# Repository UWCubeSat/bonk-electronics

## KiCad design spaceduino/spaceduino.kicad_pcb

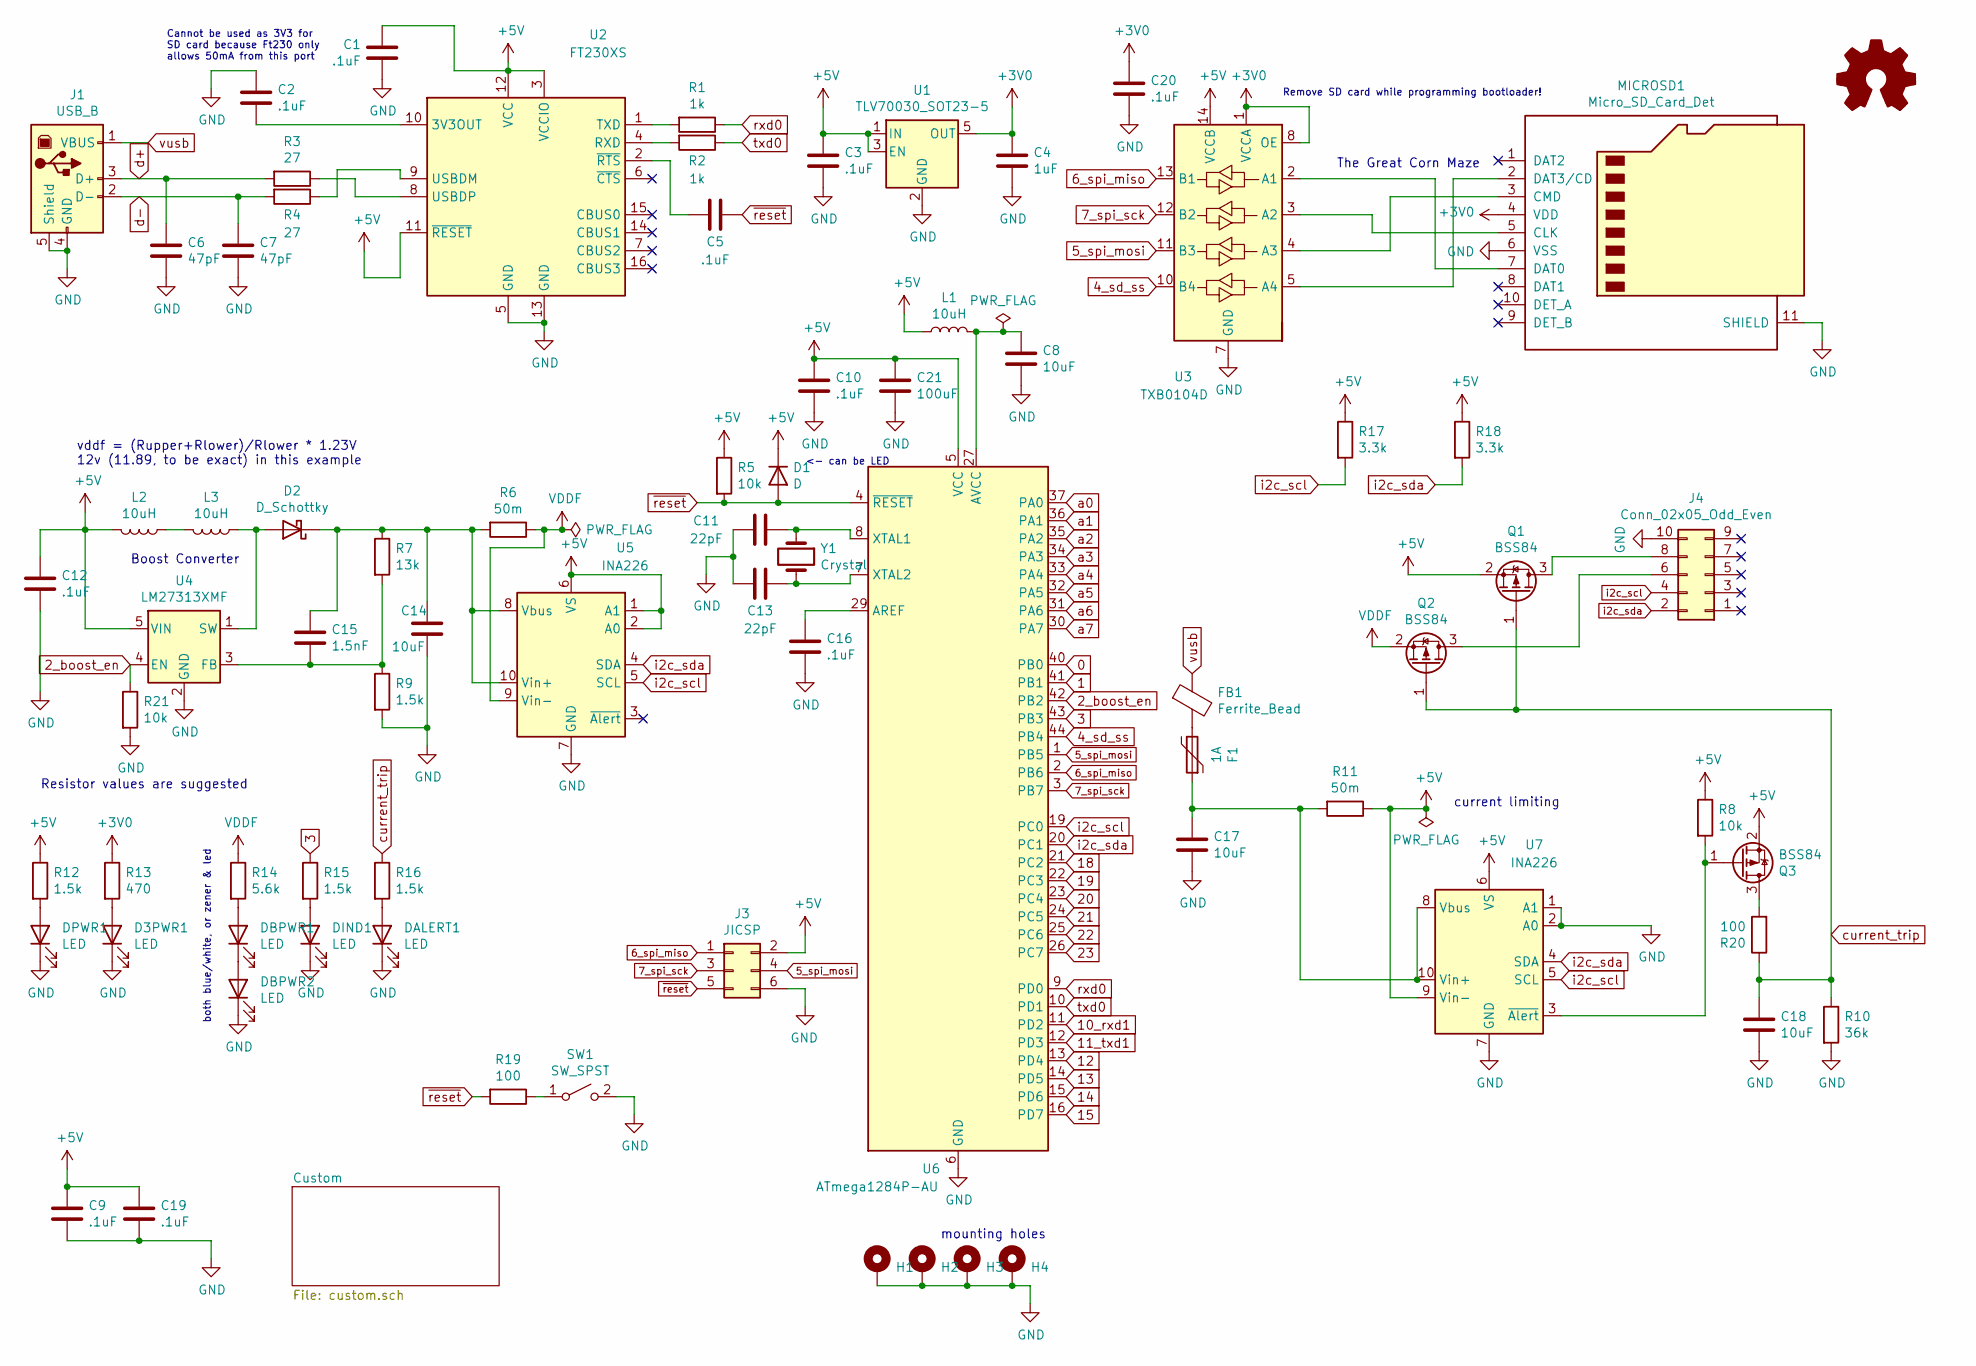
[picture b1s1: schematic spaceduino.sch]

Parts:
C1, C2, C3, C5, C9, C10, C12, C16, C19, C20: .1uF; C_0603_1608Metric; LCSC C77055
C4: 1uF; C_1206_3216Metric; LCSC C141215
C6, C7: 47pF; C_0603_1608Metric; LCSC C1671
C8, C14, C17, C18: 10uF; C_1206_3216Metric; LCSC C14860
C11, C13: 22pF; C_0603_1608Metric; LCSC C599690
C15: 1.5nF; C_0603_1608Metric; LCSC C519421
C21: 100uF; C_Radial_D5.0mm_H11.0mm_P2.00mm
D1: D; D_SOD-123
D2: D_Schottky; D_SOD-123; LCSC C222352
D3PWR1: LED; LED_1206_3216Metric; LCSC C192676
DALERT1: LED; LED_1206_3216Metric; LCSC C192676
DBPWR1, DBPWR2: LED; LED_1206_3216Metric; LCSC C192676
DIND1: LED; LED_1206_3216Metric; LCSC C192676
DPWR1: LED; LED_1206_3216Metric; LCSC C192676
F1: 1A; Fuse_1206_3216Metric; LCSC C315895
FB1: Ferrite_Bead; L_1206_3216Metric; LCSC C88995
H1, H2, H3, H4: MountingHole_Pad; MountingHole_2.2mm_M2_Pad
J1: USB_B; usb-type-b; Digikey 732-2734-ND
J3: JICSP; PinHeader_2x03_P2.54mm_Vertical
J4: Conn_02x05_Odd_Even; PinHeader_2x05_P2.54mm_Vertical
L1, L2, L3: 10uH; L_1210_3225Metric; LCSC C86073
LOGO1: Logo_Open_Hardware_Small; spaceduino-logo
MICROSD1: Micro_SD_Card_Det; HRS_DM3CS-SF; LCSC C202111
Q1, Q2, Q3: BSS84; SOT-23; LCSC C508197
R1, R2: 1k; R_1206_3216Metric; LCSC C52199
R3, R4: 27; R_1206_3216Metric; LCSC C17946
R5, R8, R21: 10k; R_1206_3216Metric; LCSC C17902
R6, R11: 50m; R_1206_3216Metric
R7: 13k; R_1206_3216Metric; LCSC C34847
R9, R12, R15, R16: 1.5k; R_1206_3216Metric; LCSC C26030
R10: 36k; R_1206_3216Metric; LCSC C18007
R13: 470; R_1206_3216Metric; LCSC C4502
R14: 5.6k; R_1206_3216Metric; LCSC C18028
R17, R18: 3.3k; R_1206_3216Metric; LCSC C26032
R19, R20: 100; R_1206_3216Metric; LCSC C17901
SW1: SW_SPST; SolderJumper-2_P1.3mm_Open_TrianglePad1.0x1.5mm
U1: TLV70030_SOT23-5; SOT-23-5; Digikey 296-32412-1-ND
U2: FT230XS; SSOP-16_3.9x4.9mm_P0.635mm; Digikey 768-1135-1-ND
U3: TXB0104D; TSSOP-14_4.4x5mm_P0.65mm; Digikey 296-21928-1-ND
U4: LM27313XMF; SOT-23-5
U5, U7: INA226; VSSOP-10_3x3mm_P0.5mm
U6: ATmega1284P-AU; TQFP-44_10x10mm_P0.8mm; Digikey ATMEGA1284P-AURCT-ND
Y1: Crystal; Crystal_HC49-U_Vertical

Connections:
0: U6.40 (PB0)
1: U6.41 (PB1)
2_boost_en: R21.1, U4.4 (EN), U6.42 (PB2)
3: R15.1, U6.43 (PB3)
4_sd_ss: U3.10 (B4), U6.44 (PB4)
5_spi_mosi: J3.4, U3.11 (B3), U6.1 (PB5)
6_spi_miso: J3.1, U3.13 (B1), U6.2 (PB6)
7_spi_sck: J3.3, U3.12 (B2), U6.3 (PB7)
10_rxd1: U6.11 (PD2)
11_txd1: U6.12 (PD3)
12: U6.13 (PD4)
13: U6.14 (PD5)
14: U6.15 (PD6)
15: U6.16 (PD7)
18: U6.21 (PC2)
19: U6.22 (PC3)
20: U6.23 (PC4)
21: U6.24 (PC5)
22: U6.25 (PC6)
23: U6.26 (PC7)
+3V0: C4.1, C20.1, MICROSD1.4 (VDD), R13.1, U1.5 (OUT), U3.1 (VCCA), U3.8 (OE)
+5V: C1.1, C3.1, C9.1, C10.1, C12.1, C19.1, C21.1, D1.1 (K), J3.2, L1.1, L2.2, Q1.2 (S), Q3.2 (S), R5.1, R8.1, R11.1, R12.1, R17.1, R18.1, U1.1 (IN), U1.3 (EN), U2.3 (VCCIO), U2.11 (~RESET), U2.12 (VCC), U3.14 (VCCB), U4.5 (VIN), U5.1 (A1), U5.2 (A0), U5.6 (VS), U6.5 (VCC), U6.17 (VCC), U6.38 (VCC), U7.6 (VS), U7.9 (Vin-)
GND: C1.2, C2.1, C3.2, C4.2, C6.2, C7.2, C8.2, C9.2, C10.2, C11.2, C12.2, C13.2, C14.2, C16.2, C17.2, C18.2, C19.2, C20.2, C21.2, D3PWR1.1 (K), DALERT1.1 (K), DBPWR2.1 (K), DIND1.1 (K), DPWR1.1 (K), H1.1, H2.1, H3.1, H4.1, J1.4 (GND), J1.5 (Shield), J3.6, J4.10, MICROSD1.6 (VSS), MICROSD1.11 (SHIELD), R9.2, R10.2, R21.2, SW1.2 (B), U1.2 (GND), U2.5 (GND), U2.13 (GND), U3.7 (GND), U4.2 (GND), U5.7 (GND), U6.6 (GND), U6.18 (GND), U6.28 (GND), U6.39 (GND), U7.1 (A1), U7.2 (A0), U7.7 (GND); also elsewhere on the board
unnamed: C2.2, U2.10 (3V3OUT)
unnamed: C5.2, U2.2 (~RTS)
unnamed: C8.1, L1.2, U6.27 (AVCC)
unnamed: C11.1, U6.8 (XTAL1), Y1.1
unnamed: C13.1, U6.7 (XTAL2), Y1.2
unnamed: C14.1, C15.1, D2.1 (K), R6.2, R7.1, U5.8 (Vbus), U5.10 (Vin+)
unnamed: C15.2, R7.2, R9.1, U4.3 (FB)
unnamed: C16.1, U6.29 (AREF)
unnamed: C17.1, F1.1, R11.2, U7.8 (Vbus), U7.10 (Vin+)
unnamed: D2.2 (A), L3.1, U4.1 (SW)
unnamed 33: DBPWR1.1 (K), DBPWR2.2 (A); also elsewhere on the board
unnamed: D3PWR1.2 (A), R13.2
unnamed: DALERT1.2 (A), R16.2
unnamed: DBPWR1.2 (A), R14.2
unnamed: DIND1.2 (A), R15.2
unnamed: DPWR1.2 (A), R12.2
unnamed: F1.2, FB1.2
unnamed: J4.6, Q2.3 (D)
unnamed: J4.8, Q1.3 (D)
unnamed: L2.1, L3.2
unnamed: MICROSD1.2 (DAT3/CD), U3.5 (A4)
unnamed: MICROSD1.3 (CMD), U3.4 (A3)
unnamed: MICROSD1.5 (CLK), U3.3 (A2)
unnamed: MICROSD1.7 (DAT0), U3.2 (A1)
unnamed: Q3.1 (G), R8.2, U7.3 (~Alert~)
unnamed: Q3.3 (D), R20.2
unnamed: R1.2, U2.1 (TXD)
unnamed: R2.2, U2.4 (RXD)
unnamed: R3.1, U2.8 (USBDP)
unnamed: R4.1, U2.9 (USBDM)
unnamed: R19.1, SW1.1 (A)
VDDF: Q2.2 (S), R6.1, R14.1, U5.9 (Vin-)
a0: U6.37 (PA0)
a1: U6.36 (PA1)
a2: U6.35 (PA2)
a3: U6.34 (PA3)
a4: U6.33 (PA4)
a5: U6.32 (PA5)
a6: U6.31 (PA6)
a7: U6.30 (PA7)
current_trip: C18.1, Q1.1 (G), Q2.1 (G), R10.1, R16.1, R20.1
d+: C6.1, J1.3 (D+), R3.2
d-: C7.1, J1.2 (D-), R4.2
i2c_scl: J4.4, R17.2, U5.5 (SCL), U6.19 (PC0), U7.5 (SCL)
i2c_sda: J4.2, R18.2, U5.4 (SDA), U6.20 (PC1), U7.4 (SDA)
rxd0: R1.1, U6.9 (PD0)
txd0: R2.1, U6.10 (PD1)
vusb: FB1.1, J1.1 (VBUS)
~reset: C5.1, D1.2 (A), J3.5, R5.2, R19.2, U6.4 (~RESET)

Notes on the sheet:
Boost Converter
The Great Corn Maze
Cannot be used as 3V3 for SD card because Ft230 only allows 50mA from this port
Remove SD card while programming bootloader!
vddf = (Rupper+Rlower)/Rlower * 1.23V 12v (11.89, to be exact) in this example
Resistor values are suggested
mounting holes
current limiting
<- can be LED
both blue/white, or zener & led

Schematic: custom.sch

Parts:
U8: MPD200A

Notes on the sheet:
Solder jumpers on the MPD200A are configured for maximum safe power and frequency, so we need not connect v_ctl & freq_ctl.

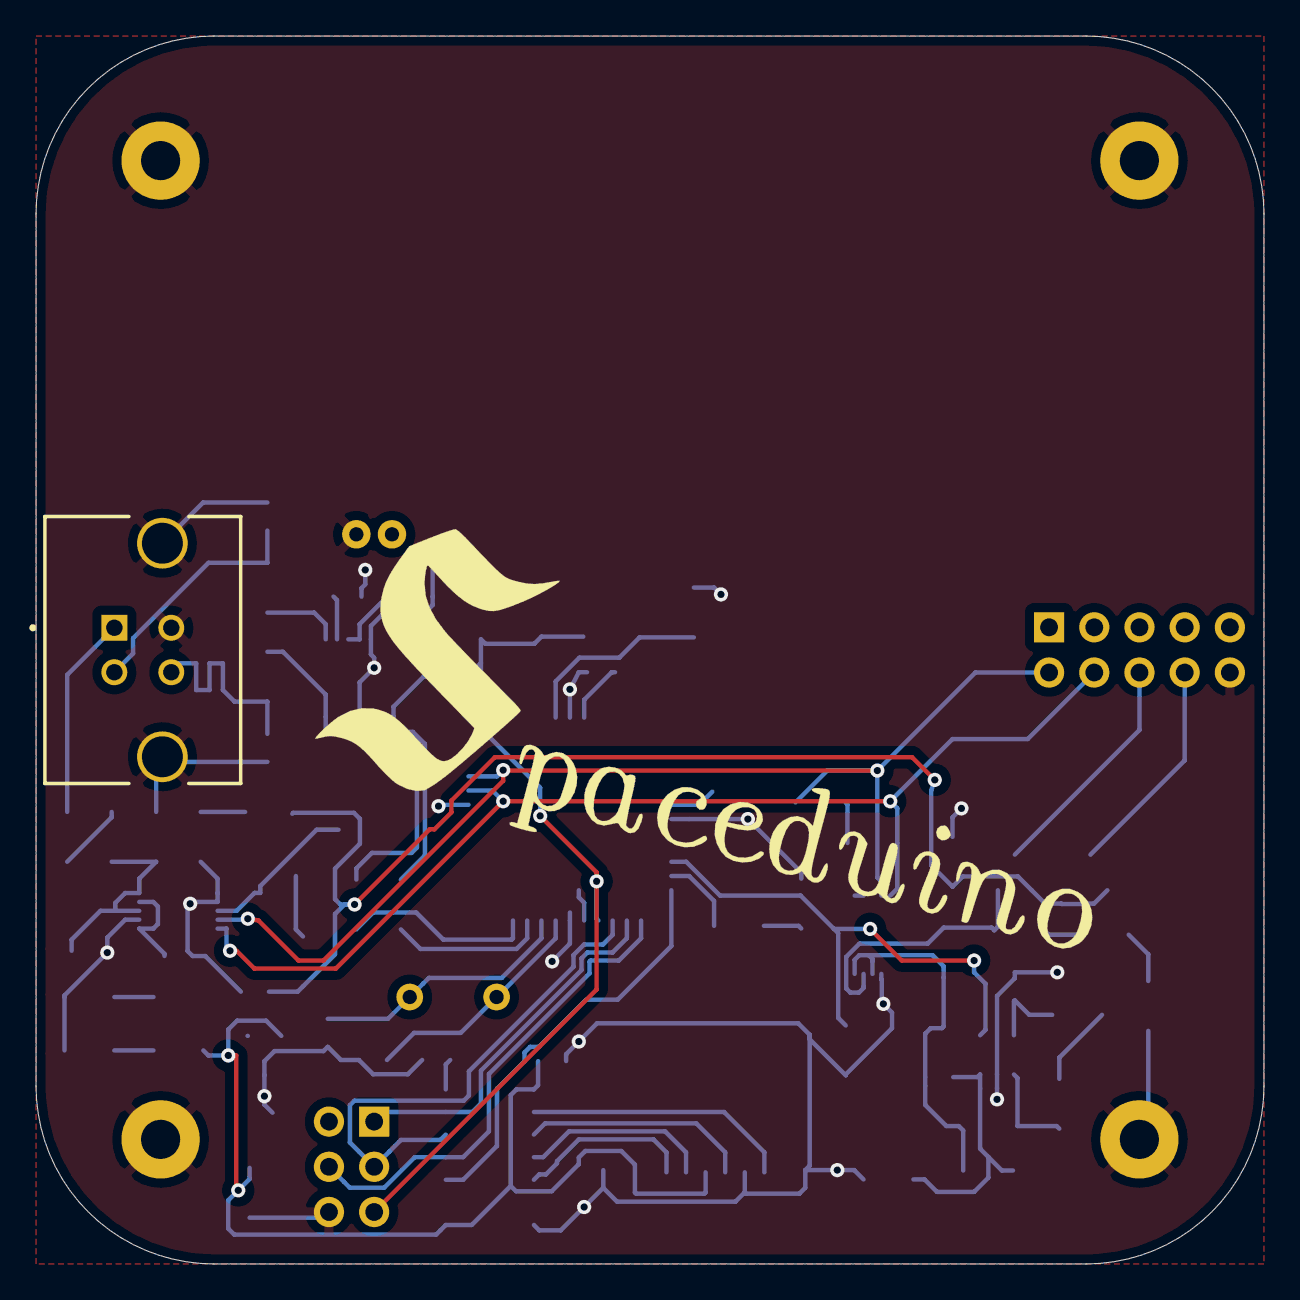
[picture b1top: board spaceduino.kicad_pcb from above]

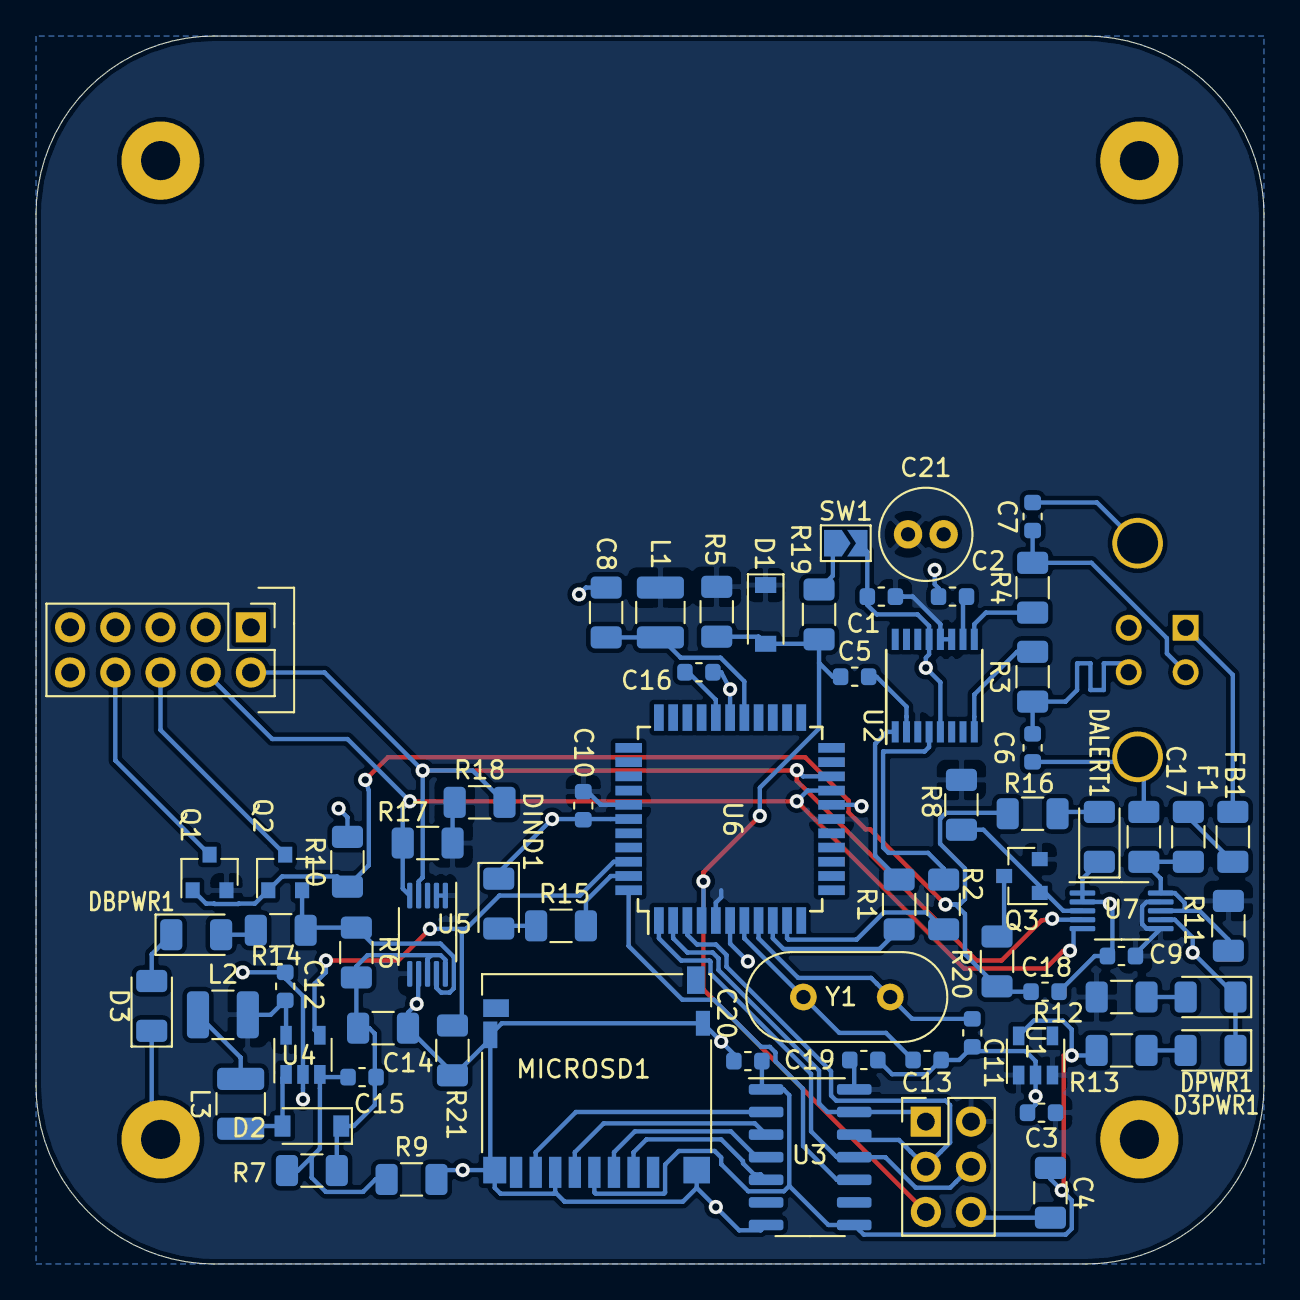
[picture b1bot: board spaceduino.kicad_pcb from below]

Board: 2 copper layers, 69.0 x 69.0 mm, 76 parts (70 on the bottom side), 50 nets.

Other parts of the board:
D3: LED; LED_1206_3216Metric

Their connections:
GND: D3.1; also elsewhere on the board
unnamed 33: D3.2; also elsewhere on the board

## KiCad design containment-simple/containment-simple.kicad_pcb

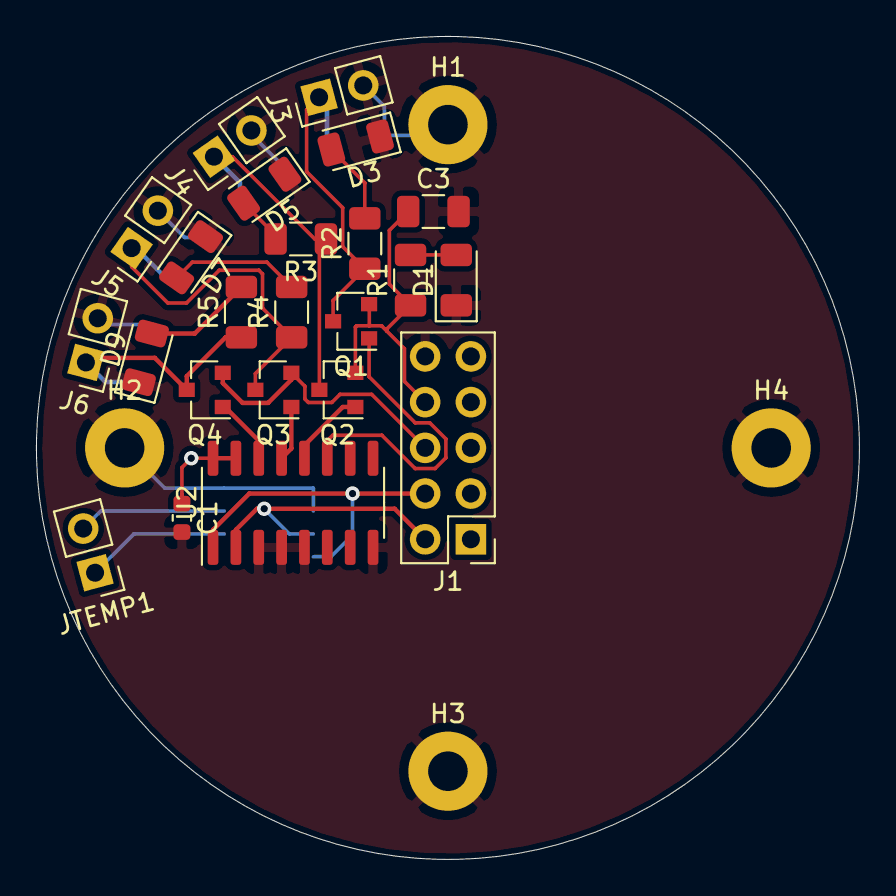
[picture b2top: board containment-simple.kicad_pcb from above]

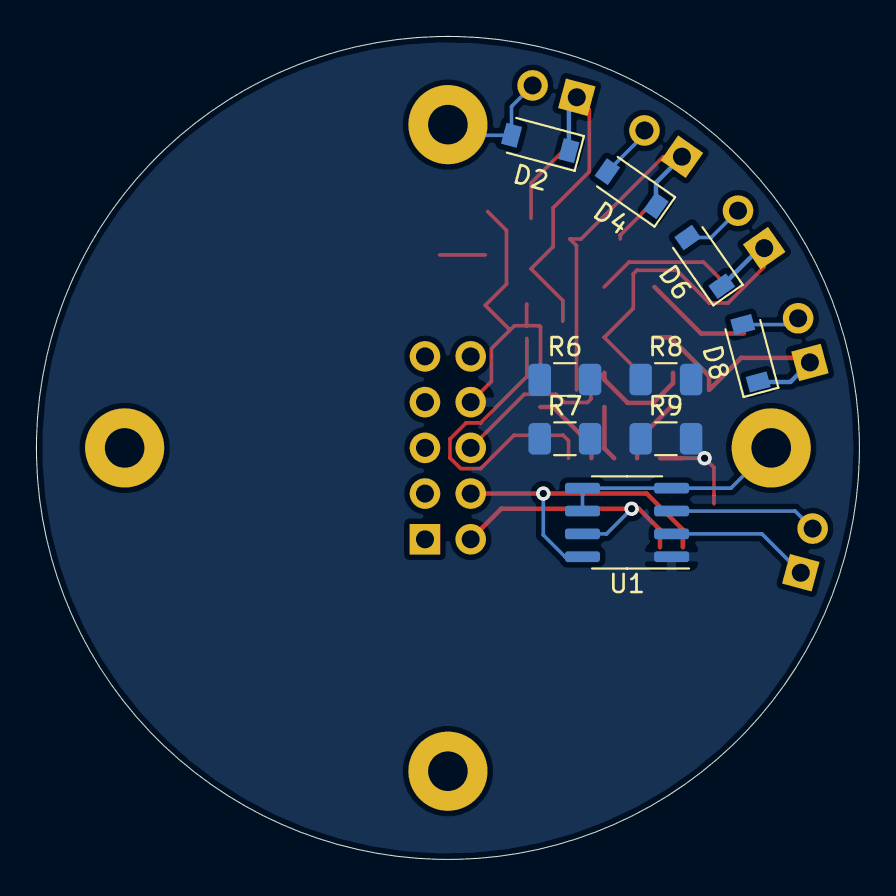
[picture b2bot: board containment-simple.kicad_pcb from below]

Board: 2 copper layers, 45.7 x 45.7 mm, 36 parts (9 on the bottom side), 24 nets.

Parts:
C1: .1uF; C_0603_1608Metric
C3: 10uF; C_1206_3216Metric
D1, D3, D5, D7, D9: LED; LED_1206_3216Metric
D2, D4, D6, D8: D; D_SOD-123
H1, H2, H3, H4: MountingHole_Pad; MountingHole_2-56_ExtraClearance
J1: Conn_02x05_Odd_Even; PinHeader_2x05_P2.54mm_Vertical
J3, J4, J5, J6: Conn_01x02; PinHeader_1x02_P2.54mm_Vertical
JTEMP1: Conn_01x02; PinHeader_1x02_P2.54mm_Vertical
Q1, Q2, Q3, Q4: BSS84; SOT-23
R1, R2, R3, R4, R5: 1k; R_1206_3216Metric
R6, R7, R8, R9: 10k; R_1206_3216Metric
U1: TMP411; SOIC-8_3.9x4.9mm_P1.27mm
U2: PCA9557; SOIC-16_3.9x9.9mm_P1.27mm

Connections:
+5V: C1.1, C3.1, J1.8, Q1.2, Q2.2, R1.1, R6.1, R7.1, R8.1, R9.1, U1.1, U2.15, U2.16
+12V: J1.6, Q3.2, Q4.2
/p0: R6.2, U2.6
/p1: R7.2, U2.7
/p2: R8.2, U2.9
/p3: R9.2, U2.10
/p4: Q1.1, U2.11
/p5: Q2.1, U2.12
/p6: Q3.1, U2.13
/p7: Q4.1, U2.14
GND: C1.2, C3.2, D1.1, D2.2, D3.1, D4.2, D5.1, D6.2, D7.1, D8.2, D9.1, H1.1, H2.1, H3.1, H4.1, J1.10, J3.2, J4.2, J5.2, J6.2, U1.4, U1.5, U1.6, U2.3, U2.4, U2.5, U2.8
unnamed: D1.2, R1.2
unnamed: D2.1, J3.1, Q1.3, R2.1
unnamed: D3.2, R2.2
unnamed: D4.1, J4.1, Q2.3, R3.1
unnamed: D5.2, R3.2
unnamed: D6.1, J5.1, Q3.3, R4.1
unnamed: D7.2, R4.2
unnamed: D8.1, J6.1, Q4.3, R5.1
unnamed: D9.2, R5.2
unnamed: JTEMP1.1, U1.2
unnamed: JTEMP1.2, U1.3
scl: J1.4, U1.8, U2.1
sda: J1.2, U1.7, U2.2

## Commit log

2020-07-09 sntuff
2020-07-24 something
2020-07-27 containment inter
2020-07-27 containment simple mostly done
2020-07-27 spaceduino simple finished
2020-07-28 spaceduino Rev. 1
2020-07-28 jk, /this/ is the spaceduino 1.0! (actually, just look at git tags)
2020-07-28 ok, flipped a mosfet, NOW im done
2020-08-15 dummy experiment versions, set up .gitignore
2020-08-27 add an extra inductor for the boost converter
2020-10-16 desktop todo added
2020-10-16 update TODO from laptop too
2020-12-20 some lcsc stuff
2020-12-20 added that cool locking sd card footprint
2020-12-20 more lcsc, redo a lot of inner containment
